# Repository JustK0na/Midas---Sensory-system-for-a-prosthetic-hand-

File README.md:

# Midas -- Sensory system for a prosthetic hand

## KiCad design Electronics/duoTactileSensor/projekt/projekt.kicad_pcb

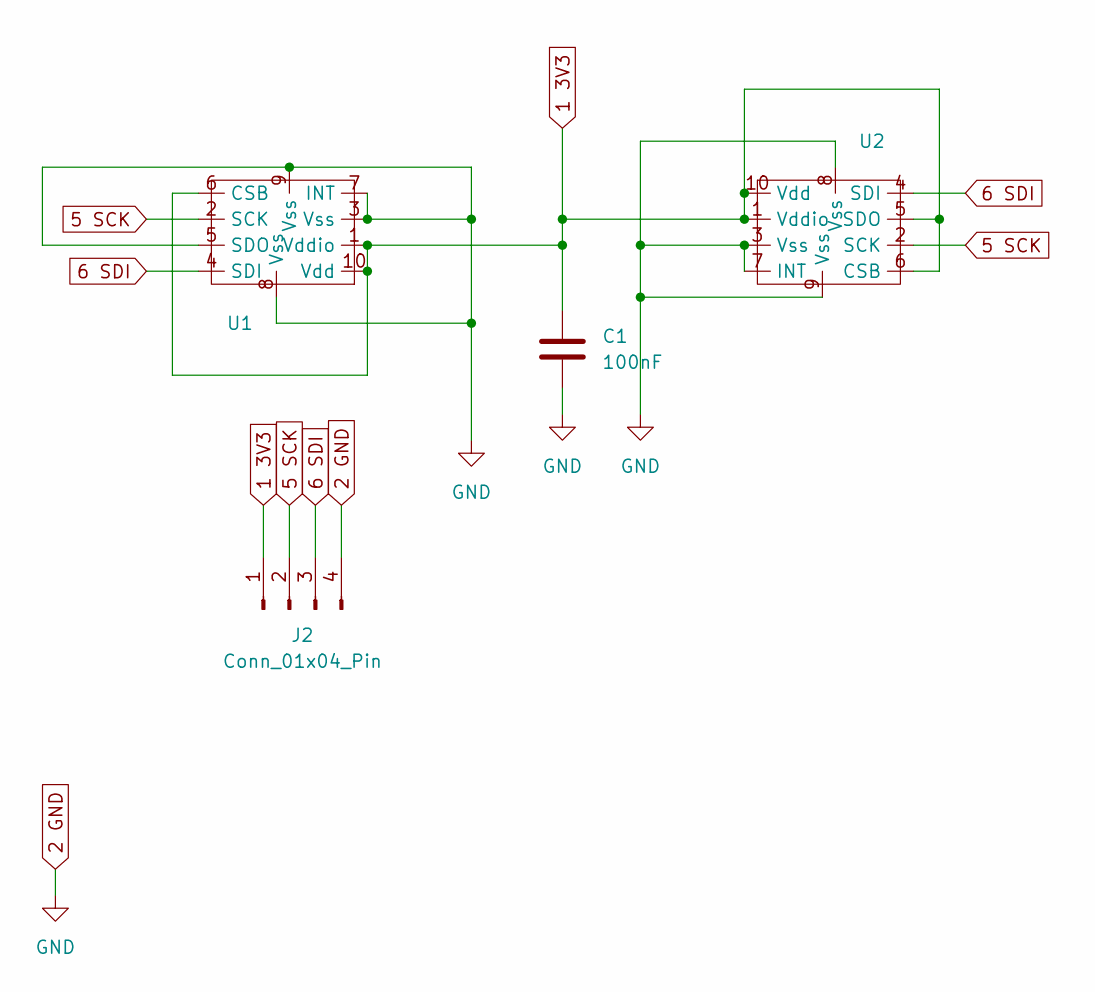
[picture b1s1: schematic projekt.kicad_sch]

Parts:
C1: 100nF; C_0805_2012Metric
J2: Conn_01x04_Pin; 4padyBMP581
U1, U2: ST_HLGA-10_2x2mm_P0.5mm_LayoutBorder3x2y

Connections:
1 3V3: C1.1, J2.1, U1.1 (Vddio), U1.6 (CSB), U1.10 (Vdd), U2.1 (Vddio), U2.5 (SDO), U2.6 (CSB), U2.10 (Vdd)
2 GND: C1.2, J2.4, U1.3 (Vss), U1.5 (SDO), U1.7 (INT), U1.8 (Vss), U1.9 (Vss), U2.3 (Vss), U2.7 (INT), U2.8 (Vss), U2.9 (Vss)
5 SCK: J2.2, U1.2 (SCK), U2.2 (SCK)
6 SDI: J2.3, U1.4 (SDI), U2.4 (SDI)

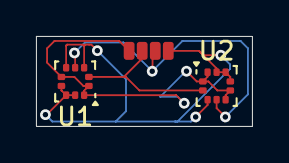
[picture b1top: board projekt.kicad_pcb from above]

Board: 2 copper layers, 12.0 x 5.0 mm, 4 parts (1 on the bottom side), 4 nets.

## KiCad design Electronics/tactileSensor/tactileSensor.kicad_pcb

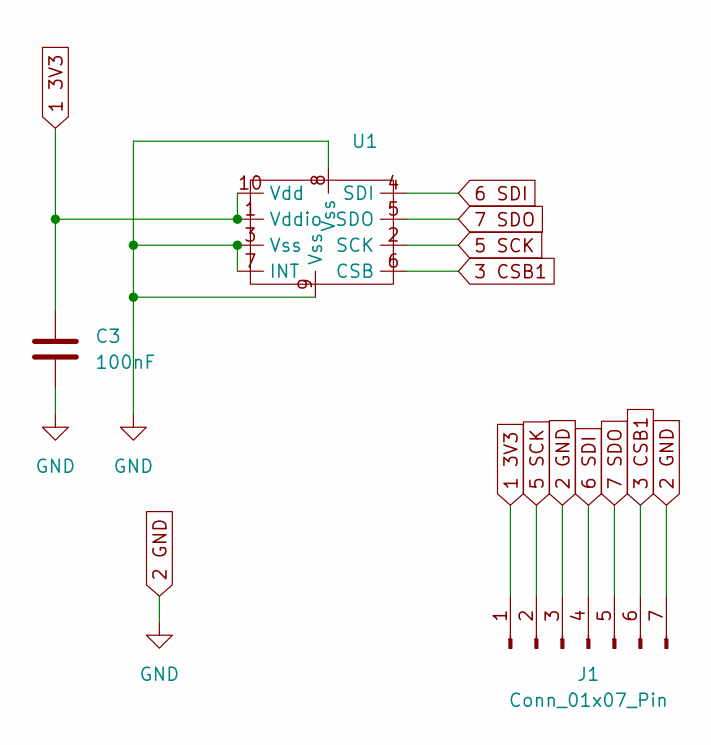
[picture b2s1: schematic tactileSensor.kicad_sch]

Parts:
C3: 100nF; C_0805_2012Metric
J1: Conn_01x07_Pin; padyBMP581
U1: ST_HLGA-10_2x2mm_P0.5mm_LayoutBorder3x2y

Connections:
1 3V3: C3.1, J1.1, U1.1 (Vddio), U1.10 (Vdd)
2 GND: C3.2, J1.3, J1.7, U1.3 (Vss), U1.7 (INT), U1.8 (Vss), U1.9 (Vss)
3 CSB1: J1.6, U1.6 (CSB)
5 SCK: J1.2, U1.2 (SCK)
6 SDI: J1.4, U1.4 (SDI)
7 SDO: J1.5, U1.5 (SDO)

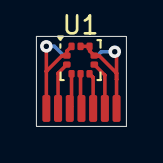
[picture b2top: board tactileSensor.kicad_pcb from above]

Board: 2 copper layers, 5.0 x 5.0 mm, 3 parts (1 on the bottom side), 6 nets.

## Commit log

2025-09-09 Basic research
2025-10-11 added simple ascii visualization of pressure
2025-10-12 added dr wolczowski's articles about prostetic hand and sensors
2025-10-21 directories reorganization
2025-10-21 Qt basics
2025-10-22 Qt basics and Raspberry directory
2025-10-25 added electronic schematics
2025-10-26 pinoutDiagram for senso
2025-10-27 Qt TCP server and client for raspberry pi
2025-10-27 ready schematic for board 4Wire SPI
2025-11-24 PCB for mini sensor
2025-11-30 RaspberryPi check sensors
2025-12-02 Preparing Qt to recive messages
2025-12-02 working raspberryPi BMP581 program, continous sensor read, working TCP client, sending measurments to Qt server
2025-12-12 changed visualization and server to python
2025-12-18 all, last commit i hope
2025-12-18 ostatni commit?
2026-04-29 duoSensor added
2026-04-29 ready to print dual Sensor PCB
2026-05-17 dodane do raportu z podwojnymi czujnikami
2026-05-17 new version with i2c now works with graphical server
